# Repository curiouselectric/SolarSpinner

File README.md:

# SolarSpinner
Solar powered Motor controller with circuit diagram, PCB and code.
This is based upon the ATTiny85, with code written and uploaded via the Arduino IDE.

This design is for a reporgrammable unit which can do different tasks, powered by a small solar PV cell and an ultra-capacitor.

The unit has an LED output, a Motor control output and a Piezo buzzer output.

## Files Included:

* PCB files (KiCAD required)
* Software (Arduino IDE with ATTiny extension required)
* Hardware (DXF files)
* Instructions (for the final device!)

## Pin out#

ATTiny85 Arduino Pins:

|IC Pin:       |Arduino Ref: | Attached:  |
|--------------|-------------|------------|
|1             |   5/A0/RST  |            |
|2             |   3/A3      | Vsolar     |
|3             |   4/A2      | Vcap       |
|4             |  GND        |            |
|5             |   0 - PWM   | Piezo      |
|6             |   1 - PWM   | Motor      |
|7             |  2/A1       | LED        |
|8             |   +Supply   |            |

## Software Modes

Note: There are only 3 sleep modes for the ATTiny25/45/85

These are: IDLE, ADC power down and Power-Down

If we want to use the PWM to give an output then we need to use IDLE.

See datasheet for more details: http://www.atmel.com/images/atmel-2586-avr-8-bit-microcontroller-attiny25-attiny45-attiny85_datasheet.pdf

### Motor Control

This runs a motor using stored power in the capacitor.
When the Vcap voltage is above a certain amount the motor is run unit the voltage drops.

Control is as follows:

* Wake up on Watch Dog Timer (every set time (0.5 or 1 second)
* If Vcap > Vhigh start with PWM = 255 (fully on) & set motor = ON
* If Vcap < Vhigh & motor is ON then reduce the PWM from 255 by 1 (down to a minimum speed)
* If Vcap < Vlow then switch off the unit & set motor = OFF
* Enter sleep

### LED Nightlight

Automatically switches on an LED when the solar input is low. This will run until the capacitor voltage is too low.

Control is as follows:

* Wake up on Watch Dog Timer (every set time (0.5 or 1 second)
* If Vcap > Vhigh && Vpv < Von setpoint then LED = ON
* If Vpv > V off set point then LED = OFF
* If Vcap < Vlow then switch off LED = OFF
* Enter sleep

### Solar Cricket

'Chrips' a noise (using a piezo element attached to the motor connections) when there is sunlight. Rate and pitch of chirping depends upon solar input. Lower solar = lower pitch chirp and lower rate of chirp.
Control is as follows:

* Wake up on Watch Dog Timer (every set time (0.5 or 1 second)
* If Vcap > Vhigh start 'chirp'. 'chirp' frequency is set by Vpv
* 
* If Vcap < Vlow then switch off the unit & set motor = OFF
* Enter sleep

### Nighttime Cricket

'Chirps' a noise (using a piezo element attached to the motor connections) when the solar voltage is low (dark). Does this until the capacitor runs out.
Control is as follows:

* Wake up on Watch Dog Timer (every set time (0.5 or 1 second)
* If Vcap > Vhigh start with PWM = 255 (fully on) & set motor = ON
* If Vcap < Vhigh & motor is ON then reduce the PWM from 255 by 1 (down to a minimum speed)
* If Vcap < Vlow then switch off the unit & set motor = OFF
* Enter sleep

### Ultrasonic Bug Repeller

Some animals (cats, dogs, rats) and insects (mosquittos) respond to different ultrasonic frequencies of sound.
https://en.wikipedia.org/wiki/Electronic_pest_control
Some people question the effectiveness of this, so this is here for a bit of a trial, really - see what you think!

Control is as follows:

* Wake up on Watch Dog Timer (every set time (0.5 or 1 second)
* If Vcap > Vhigh start repller = ON
* If repeller = ON  then Set PWM = random time between 40-255
* If Vcap < Vlow then switch off the unit & set motor = OFF
* Enter sleep

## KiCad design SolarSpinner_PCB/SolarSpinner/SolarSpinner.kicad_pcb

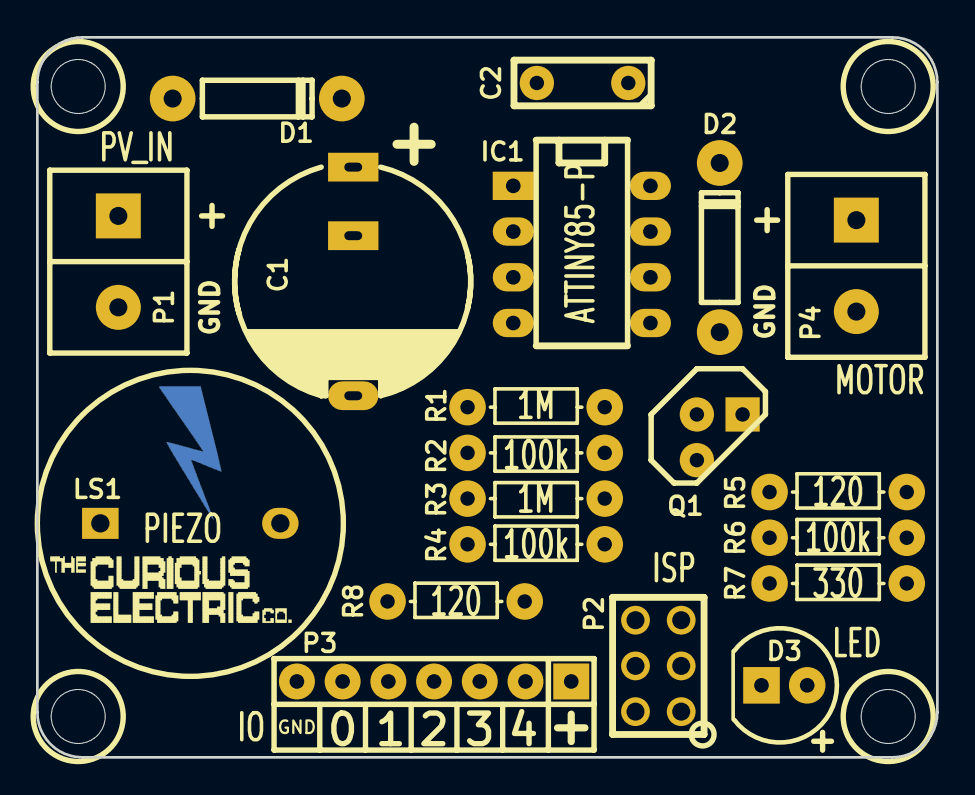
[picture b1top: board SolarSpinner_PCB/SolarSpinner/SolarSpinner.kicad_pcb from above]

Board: 2 copper layers, 50.0 x 40.0 mm, 23 parts (0 on the bottom side), 13 nets, no tracks yet.

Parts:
C1: 0.47F; C_0_47F_SuperCap_2POS
C2: 100n; C1_wide_lg_pad_2
D1: 1N5819; TH_Diode_1
D2: 1N4001; TH_Diode_1
D3: LED; TH_LED-5MM_larg_pad
IC1: ATTINY85-P; DIP-8_300_ELL
LS1: PIEZO; TH_PIEZO_17x7
P1: PV_IN; SIL-2_screw_terminal
P2: ISP; ISP_3x2
P3: IO; SIL-7_DIO
P4: MOTOR; SIL-2_screw_terminal
P5: HOLES; PCB_Holes_40x50
P6: LOGO1; 2019_011_16_CuriousElectricCompany_Logo_Round_Logo_No_words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
P7: LOGO2; TCEC_Words_13mm
Q1: BC547; TO92-EBC_large_pad
R1, R3: 1M; TH_Resistor_1
R2, R4, R6: 100k; TH_Resistor_1
R5, R8: 120; TH_Resistor_1
R7: 330; TH_Resistor_1

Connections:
/LED: IC1.7, P2.3, P3.4, R7.1
/MOTOR: IC1.6, P2.1, P3.5, R5.1
/PIEZO: IC1.5, P2.4, P3.6, R8.1
/Vin: IC1.2, P3.3, R3.1, R4.2
/Vsolar: IC1.3, P3.2, R1.1, R2.2
GND: C1.2, C2.2, D3.1, IC1.4, LS1.2, P1.2, P2.6, P3.7, Q1.3, R2.1, R4.1, R6.1
unnamed: D1.2, P1.1, R1.2
unnamed: D2.1, P4.2, Q1.1
unnamed: D3.2, R7.2
unnamed: IC1.1, P2.5
unnamed: LS1.1, R8.2
unnamed: Q1.2, R5.2, R6.2
VCC: C1.1, C2.1, D1.1, D2.2, IC1.8, P2.2, P3.1, P4.1, R3.2

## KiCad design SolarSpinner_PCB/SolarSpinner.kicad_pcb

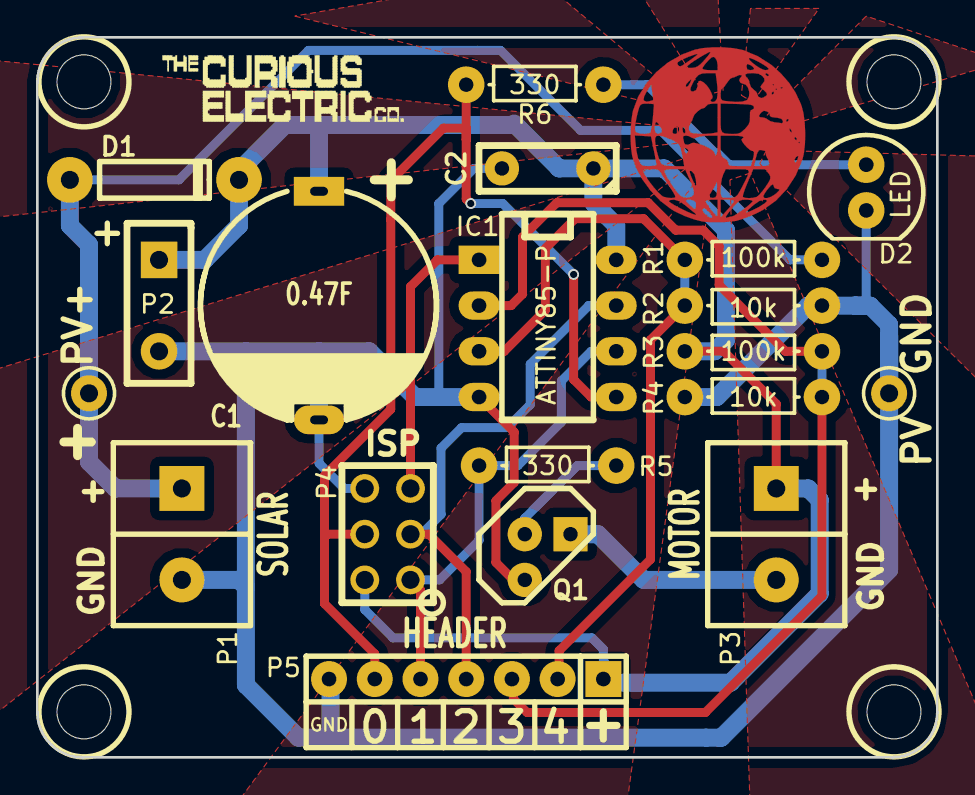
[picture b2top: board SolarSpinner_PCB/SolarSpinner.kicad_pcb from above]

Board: 2 copper layers, 50.0 x 40.0 mm, 21 parts (0 on the bottom side), 12 nets.

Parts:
C1: 0.47F; C_0_47F_SuperCap
C2: 100n; C1_wide_lg_pad
D1: 1N5819; TH_Diode_1
D2: LED; LED-5MM_larg_pad
IC1: ATTINY85-P; DIP-8_300_ELL
P1: SOLAR; SIL-2_screw_terminal
P2: SOLAR_V; SIL-2_wide_lg_pad
P3: MOTOR; SIL-2_screw_terminal
P4: ISP; ISP_3x2
P5: HEADER; SIL-7_DIO
P7: LOGO1; CEC_Globe_10mm_FCU
P8: LOGO2; TCEC_Words_13mm
P10: HOLES; PCB_Holes_40x50
Q1: BC547; TO92-EBC_large_pad
R1, R3: 100k; TH_Resistor_1
R2, R4: 10k; TH_Resistor_1
R5, R6: 330; TH_Resistor_1
SC1: PV_CELL; PV_50x30mm_round

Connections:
/MOTOR: IC1.6, P4.1, P5.5, R5.1
/Vin: IC1.2, P5.3, R3.1, R4.2
/Vsolar: IC1.3, P5.2, R1.1, R2.2
GND: C1.2, C2.2, D2.1, IC1.4, P1.2, P2.2, P4.6, P5.7, Q1.3, R2.1, R4.1, SC1.2
unnamed: D1.2, P1.1, R1.2, SC1.1
unnamed: D2.2, R6.2
unnamed: IC1.1, P4.5
unnamed: IC1.5, P4.4, P5.6, R6.1
unnamed: IC1.7, P4.3, P5.4
unnamed: P3.2, Q1.1
unnamed: Q1.2, R5.2
VCC: C1.1, C2.1, D1.1, IC1.8, P2.1, P3.1, P4.2, P5.1, R3.2

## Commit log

2017-06-11 Initial comit
2017-06-11 Adding code
2017-08-18 Updated PCB
2017-08-18 Updated hardware
2017-08-18 Updated PCB. New Gerber
2020-11-19 Large update of tests
2020-11-19 Moving file structure
2020-11-19 Done libraries for functions
2020-11-19 Slight update of libraries
2020-11-20 small update
2020-11-20 Code Update for different functions
2020-11-20 Removed old tests
2020-11-22 Update of tests
2020-11-22 Update of PCB and schematic
2020-11-24 updated code for solar spinner
